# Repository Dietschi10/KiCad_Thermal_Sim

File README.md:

# KiCad Thermal Sim - Fast Multi-Layer Copper Thermal Simulation for KiCad

**KiCad Thermal Sim** is a lightweight KiCad PCB Editor plugin for fast, layout-oriented **heat spreading simulation across all copper layers** (`F.Cu` to `B.Cu`, including inner layers).

This is **not** a full 3D CFD/FEA solver. It is intended as a practical engineering tool to quickly answer:

- Where are the **hotspots** on each copper layer?
- How much do **copper pours/planes** and **via stitching** help?
- Which layout variant is **better** in an A/B comparison?
- How does heat distribute through the **stackup**?
- How much extra heat is created by **DC current flow** in copper?
- Which grid settings were actually used when automatic coarsening protects runtime?

---

## What It Simulates

- **2D in-plane conduction** on each copper layer.
- **Vertical coupling** between adjacent copper layers through FR4 and via enhancement.
- **Manual power injection** from explicitly configured **Heat Sources**.
- Constant pad power and time-varying **PWL power profiles**.
- Optional **DC current-flow heating** from source/sink pads on KiCad nets.
- **Convection** to ambient on top and bottom outer surfaces.
- Optional **Thermal Pad** geometry on `User.Eco1` for stronger bottom-side heat removal.
- Current-path diagnostics: copper loss, effective resistance, equivalent voltage drop, grid quality, and a Joule loss map.

---

## Installation

### Option A: KiCad Plugin Manager

1. Download the latest `ThermalSim-vX.Y.Z.zip` from the [Releases](https://github.com/PoeAlex/KiCad_Thermal_Sim/releases) page.
2. In KiCad, open **Plugin and Content Manager**.
3. Click **Install from File...** and select the downloaded ZIP.
4. Restart KiCad.
5. On first run, the plugin detects missing dependencies and offers to install them automatically.

### Option B: Manual Copy

1. Download or clone this repository.
2. Copy the plugin folder, meaning the folder that contains `__init__.py`, `thermal_plugin.py`, and the other `.py` modules, into KiCad's plugin directory:

   - **Windows**: `%APPDATA%\kicad\9.0\scripting\plugins\`
   - **Linux**: `~/.local/share/kicad/9.0/scripting/plugins/`
   - **macOS**: `~/Library/Application Support/kicad/9.0/scripting/plugins/`

3. Restart KiCad.
4. On first run, the plugin offers to install missing packages (`numpy`, `scipy`, `matplotlib`) automatically.

Alternatively, install packages manually in the **KiCad 9.0 Command Prompt**:

```bash
pip install numpy scipy matplotlib
```

Optional for faster large solves on supported Windows/Linux x86_64 systems:

```bash
pip install pypardiso
```

Run the plugin in PCB Editor via **Tools -> External Plugins -> 2.5D Thermal Sim**.

---

## Quick Start

1. Open your PCB in **KiCad PCB Editor**.
2. Select one or more pads if you want to pre-fill manual heat sources.
3. Run **Tools -> External Plugins -> 2.5D Thermal Sim**.
4. Use **Heat Sources** to add pads that dissipate manual power, then enter constant W values or PWL file paths.
5. Set **Duration**, **Ambient**, and **Resolution** on the **Overview** tab.
6. Optionally use **Current Heating** to add source/sink pads and per-pad currents for copper `I^2R` heating.
7. Optionally use **Advanced** for the simulation area, thermal pad, convection, and solver settings.
8. If current heating is enabled, click **Electrical Preview** to check current-net connectivity.
9. Click **Thermal Geometry Preview** to check the mapped board area, then **Run Simulation**.

---

## GUI Settings

The resizable dialog keeps board context and live preflight status visible above and below four compact tabs:

- **Overview** - duration, ambient temperature, target cell size, compute budget, live cost estimate, output, and collapsible board details.
- **Heat Sources** - manual heat sources selected independently from current terminals.
- **Current Heating** - DC current source/sink terminals for Joule heating.
- **Advanced** - collapsible simulation-area, thermal-pad, and solver settings.

The header summarizes the board, copper-layer count, heat sources, and current-balance state. The fixed footer shows the requested versus actual grid, readiness warnings, and the **Electrical Preview**, **Thermal Geometry Preview**, and **Run Simulation** actions. Electrical Preview is enabled when current heating has active terminals. Help and settings import/export are available from **More**. After a successful run, the dialog retains maximum temperature, elapsed time, and shortcuts to the report and output folder.

### Overview Tab

#### Board Info

Shows detected copper layers with thicknesses and dielectric gaps parsed from the board stackup. Pads selected when the dialog opened are shown only as a convenience; simulation roles are configured in **Heat Sources** and **Current Heating**.

#### Main Settings

- **Duration (sec)** - total simulated time. Shorter durations emphasize transient peaks; longer durations approach quasi steady-state.
- **Ambient Temp (C)** - reference temperature. Results are relative to ambient.
- **Target Cell Size (mm)** - desired spatial grid size. Smaller values improve hotspot and trace localization but increase runtime.
- **Compute Budget** - choose **Fast**, **Balanced**, **Detailed**, **Very detailed**, or **Custom**. The budget is based on total solver nodes across all copper layers.
- **Maximum Solver Nodes** - available in Custom mode for an explicit upper
  limit of up to 100 million equivalent uniform nodes. Values above 10 million
  are expert settings and may require tens of GB of RAM before adaptive
  reduction.

The live estimate shows requested versus actual cell size, grid dimensions, total nodes, approximate resolvable feature size, memory range, and a relative runtime class. For large boards, ThermalSim may automatically coarsen the requested cell size to remain within the selected budget. The report records the requested and actual resolution, compute budget, and simulated board fraction.

#### Output

- **Show All Layers** - display results for all copper layers.
- **Save Snapshots** - store intermediate temperature images.
- **Snapshot Count** - number of intermediate snapshots.
- **Output Folder** - where the timestamped result folder is created.

#### Settings Files

- **Load Settings...** - load a JSON settings file from any folder and apply it to the open dialog.
- **Save Settings...** - save the current dialog values as a JSON settings file.

ThermalSim also keeps using `thermal_sim_last_settings.json` in the plugin folder for automatic last-used settings. Manual load/save files use the same JSON structure and can be stored per project or per experiment.

### Heat Sources Tab

Manual pad power is configured separately from current-flow terminals.

1. Select pads in KiCad.
2. Click **Add Selected**.
3. Enter a power value or PWL file path in **Power / PWL**.
4. Use **Apply** to write the value to selected table rows. If no row is selected, a comma-separated list is applied in table order.

The Heat Sources table is:

| Column | Meaning |
|--------|---------|
| Pad | Footprint/pad name |
| Net | KiCad net name |
| Layer | Pad layer |
| Power W/PWL | Constant W value or PWL file path |

Accepted power entries:

| Entry | Meaning |
|-------|---------|
| `1.0` | 1 W constant on selected/listed power pads |
| `1.0, 0.5, 2.0` | Per-pad constant power in table order |
| `C:\sim\ramp.pwl` | Same PWL profile for selected/listed pads |
| `1.0, C:\sim\ramp.pwl` | Pad 1 = 1 W constant, Pad 2 = PWL file |

For backward compatibility, pads selected before opening the dialog pre-fill the Heat Sources table when no saved `power_pads` setting exists.

#### PWL File Format

PWL files are LTspice-style text files with two columns:

```text
; Comment lines start with ; or *
; Time(s)  Power(W)
0.0        0.0
0.001      1.0
0.005      2.5
0.010      2.5
0.020      0.0
```

- Time is in seconds.
- Power is in watts.
- Time values must be monotonically increasing.
- Power is linearly interpolated between points and held at the first/last value outside the defined range.

### Current Heating Tab

Enable current heating to calculate copper losses from DC current flow.

1. Select source/sink pads in KiCad.
2. Add them to a current group.
3. Enter positive current for source pads and negative current for sink pads.
4. Make sure every active KiCad net balances to `0 A`.

Current heating is additive with **Heat Sources**:

```text
total heat = manual pad power + calculated Joule copper loss
```

Power pads and current terminals may be different pads. Area limiting remains available with current heating: ThermalSim includes every pad, track, via/PTH, and filled zone belonging to the active current nets, then expands that geometry by the configured thermal margin. A large active plane may therefore require almost the full board.

The report shows **Path Current** as the useful current value. For a `+5 A` source and a `-5 A` sink, the path current is `5 A`. The internal sum of absolute terminal currents (`10 A` in that example) is kept only in raw diagnostics.

### Advanced Tab

#### Geometry Filters

- **Ignore Traces** - exclude copper traces from the conductivity map; zones, pours, and pads still contribute.
- **Limit to Active Sources and Current Paths** - crop the rectangular solver domain around heat sources and complete active current-net geometry.
- **Thermal Margin (mm)** - additional board area around sources and current paths. A practical starting point is 10-30 mm.

The preflight status shows the effective dimensions and percentage of the board. All copper inside the rectangular domain remains part of the thermal model. If active-net geometry cannot be inspected safely, ThermalSim falls back to the full board and reports a warning.

#### Thermal Pad (`User.Eco1`)

- **Enable Pad Simulation** - treat `User.Eco1` geometry as a thermal interface zone with enhanced bottom-side heat removal.
- **Pad Thickness (mm)** - thermal interface thickness.
- **Pad Cond. (W/mK)** - thermal interface conductivity.
- **Pad Heat Cap. (J/m2K)** - additional areal heat capacity.

#### Solver

- **Convection h (W/m2K)** - convection coefficient for top/bottom surfaces. Default is 10.
- **PCB Thickness (mm)** - overall board thickness. Stackup thickness is used when available.
- **Compute Engine** - `Auto` selects the matrix-free CPU engine for large jobs and keeps the legacy sparse solver for small jobs. Both engines remain manually selectable.
- **Spatial Mesh** - `Adaptive` keeps the requested cell size at copper edges, pads, vias, sources, and thermal-pad boundaries while merging homogeneous interiors. `Uniform` keeps the full regular grid.
- **Adaptive Max Cell Ratio** - largest adaptive cell relative to the requested cell size. The default is 8.
- **Capabilities** - detected solver backend, including the optional `thermalsim_core.dll`.

The **Balanced** compute budget is the default. Presets use total solver nodes, so a four-layer board automatically receives fewer 2D cells than a two-layer board at the same budget. **Custom** exposes one explicit maximum-node value; ThermalSim retains headroom when it must auto-coarsen.

The fast engine applies the finite-volume operator without constructing the
large global COO/CSR matrix used by the legacy direct solver. Adaptive runs use
a conservative reduced graph and geometrically coarsened multigrid
preconditioning. Reports show the equivalent uniform nodes, actual adaptive
nodes, reduction factor, PCG iterations, and residual.

---

## Previews

**Electrical Preview** checks active current-net connectivity and shows the solver's topology, graph raster, and copper occupancy. Use it before running current heating; it is enabled only when current heating has active terminals. It produces `electrical_connectivity_preview.png`, `electrical_graph_raster_preview.png`, and `electrical_copper_occupancy_preview.png`.

The synthetic regression board is available at `tests/demo/synthetic_electrical_connectivity_demo.kicad_pcb`.

**Thermal Geometry Preview** maps copper, power/current pads, vias, and the effective thermal simulation area. It does not run the thermal solver or show temperatures. Its header reports the cropped dimensions and percentage of the board.

Both previews use the copper-zone fills already stored by KiCad. If zones are stale or unfilled, press **B** in PCB Editor before previewing or running. The plugin does not refill zones automatically because this can block the interface for minutes on large boards and is unstable in some KiCad builds.

---

## Report Output

Each run creates a timestamped result folder, for example `Thermalsim_20260426_111121/`.

Typical files:

- `thermal_report.html` - main report with settings, stackup, diagnostics, images, and interactive heatmap.
- `thermal_preview.png` - mapped geometry preview.
- `thermal_stackup.png` or `thermal_final.png` - final temperature heatmap.
- `joule_loss_map.png` - current-induced copper loss map when current heating is active.
- `snap_*.png` - optional time-series snapshots.

### Current Path Diagnostics

When current heating is enabled, the HTML report includes **Current Path Diagnostics**:

- **Copper Loss** - total calculated Joule heating for active nets.
- **R_eff** - effective resistance, computed from `P / I_source^2`.
- **V_eq** - equivalent voltage drop, computed from `P / I_source`.
- **Source/Sink Current** - source and sink totals per active net.
- **Path Current** - useful current value for the path, not the doubled absolute terminal sum.
- **Net Path Metrics** - terminals, balance, loss, resistance, voltage drop, cell count, edge count, via edges, and copper islands.
- **Current Terminals** - pad positions, matched grid cells, island IDs, and mean potentials.
- **Mapped KiCad Primitives** - pads, tracks, vias/PTHs, zones, track length, and width summary.
- **Joule Loss Map** - per-layer static image of current-induced copper loss.

The report records requested and actual grid resolution, grid size, compute-budget preset, node budget, and the simulated percentage of the board.

---

## How to Interpret Results

This tool is most reliable for:

- **Relative comparisons** between layout variants.
- **Hotspot locations**.
- Trends from more copper, more vias, wider traces, or better spreading.
- Order-of-magnitude current-path loss and resistance diagnostics.

Absolute temperatures are **estimates** and depend strongly on modeling assumptions, grid resolution, board environment, airflow, and component/package thermal paths.

---

## Architecture

The plugin is split into focused modules:

| Module | Purpose |
|--------|---------|
| `capabilities.py` | Runtime detection of numpy, scipy, matplotlib, pypardiso, numba |
| `dependency_installer.py` | Auto-install dialog for missing packages via pip |
| `stackup_parser.py` | Parse copper/dielectric layers from `.kicad_pcb` S-expressions |
| `gui_dialogs.py` | wxPython dialog for simulation parameters |
| `geometry_mapper.py` | Accurately rasterize tracks, arcs, pads, vias, and filled zones |
| `adaptive_mesh.py` | Build conservative adaptive meshes and multigrid operators |
| `electrical_solver.py` | Solve DC current flow and convert copper losses to heat sources |
| `thermal_solver.py` | Legacy sparse and matrix-free PCG/BDF2 thermal solvers |
| `native_core.py` | Load the optional Windows x64 C++/OpenMP CPU core |
| `pwl_parser.py` | Parse LTspice-style PWL power profiles |
| `visualization.py` | Generate thermal plots, previews, heatmap payloads, and Joule loss maps |
| `thermal_report.py` | Generate the HTML report |
| `thermal_plugin.py` | Orchestrate workflow and KiCad ActionPlugin integration |

---

## Limitations

- No explicit component/package thermal model; junction-to-case-to-pad behavior is not modeled.
- Convection is simplified as uniform top/bottom ambient coupling.
- Radiation is not modeled.
- Current-flow heating is static DC only; AC effects, skin effect, and temperature-dependent copper resistance are not modeled.
- Current-path accuracy depends on grid resolution; narrow traces and small pads may need a finer grid to match hand calculations closely.
- Very fine requested resolutions may be auto-coarsened when the selected compute budget is exceeded.
- Via coupling is an approximation.
- Results depend strongly on **Target Cell Size**, **Compute Budget**, and the selected simulation area and thermal margin.
- Thermal Pad (`User.Eco1`) is a simplification of real contact pressure, interface quality, and sink temperature.

---

## Suggested Workflow

1. Add manual dissipating components in **Heat Sources**.
2. Add source/sink terminals in **Current Heating** only when copper `I^2R` heating matters.
3. Press **B** in PCB Editor so every copper zone has a current fill.
4. Enable **Limit to Active Sources and Current Paths** and start with a moderate thermal margin, for example 20 mm.
5. Check the effective board percentage; active current nets are always included completely.
6. Tune **Target Cell Size** until hotspots and current-path metrics are stable. Try 0.5 mm, then 0.3 mm.
7. Increase the **Compute Budget** only after checking the live node, memory, and runtime estimate.
8. Save JSON settings for repeatable project comparisons.
9. Compare layout variants using the same settings.
10. Validate important designs with measurement or a full 3D thermal workflow.

---

## Testing

Run the test suite from the repository root:

```bat
run_tests.bat
```

Run the synthetic large-grid benchmark without a proprietary board file:

```bash
python benchmark_fast_engine.py --nodes 10000000 --layers 4 --solve-steps 3
```

Legacy matrix construction is automatically skipped above the configured
safety limit. The benchmark reports equivalent/adaptive node counts, operator
build times, solve time, iteration counts, and process memory.

To build the optional native Windows CPU core, install Visual Studio Build
Tools with the C++ workload, then run:

```bash
cmake -S native -B native/build
cmake --build native/build --config Release
```

The generated `native/bin/thermalsim_core.dll` is included automatically by
`build_pcm_package.py`. Without the DLL, the same fast-engine interface uses
the NumPy/SciPy CPU implementation.

Useful variants:

```bat
run_tests.bat -k "test_thermal_solver"
run_tests.bat -m physics
run_tests.bat --cov=ThermalSim
```

### Real KiCad Benchmark

Use KiCad's bundled Python to benchmark a real board without saving or modifying it:

```powershell
& "C:\Program Files\KiCad\9.0\bin\python.exe" benchmark_real_board.py `
  "C:\path\to\board.kicad_pcb" --scenario thermal --time-stepping auto
```

Set `THERMALSIM_HEADLESS=1` when importing ThermalSim as a library outside PCB Editor. This prevents ActionPlugin registration while keeping the solver and board readers available.

---

## License / Disclaimer

MIT License

This plugin provides engineering estimates intended for fast iteration and comparative analysis. For safety-critical or thermally constrained designs, validate with measurement and/or a full 3D thermal tool.

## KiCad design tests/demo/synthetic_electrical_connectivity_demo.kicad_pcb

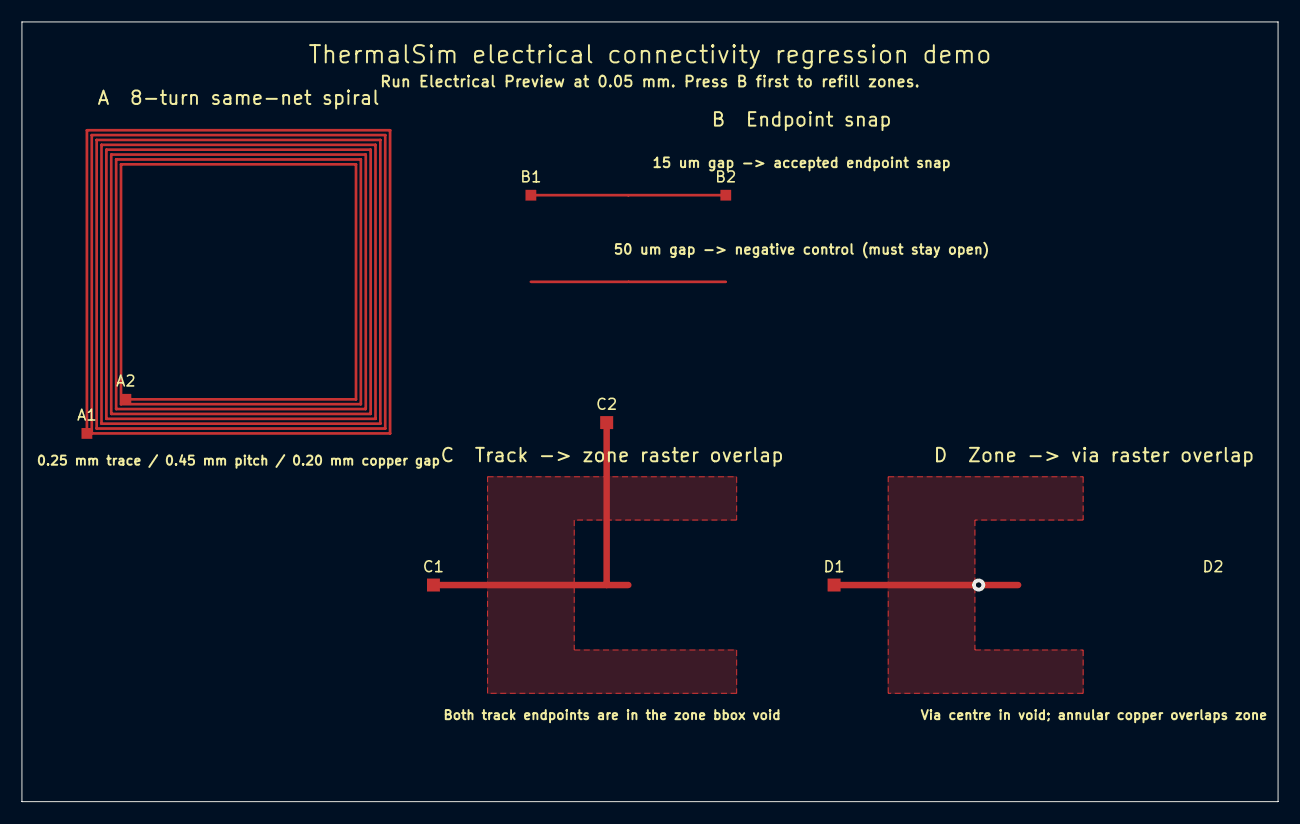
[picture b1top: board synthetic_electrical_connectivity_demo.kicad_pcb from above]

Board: 4 copper layers, 116.0 x 72.0 mm, 8 parts (0 on the bottom side), 4 nets.

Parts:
A1, A2: DEMO_A_8TURN_SPIRAL; Terminal
B1, B2: DEMO_B_15UM_SNAP; Terminal
C1, C2: DEMO_C_TRACK_ZONE; Terminal
D1, D2: DEMO_D_ZONE_VIA; Terminal

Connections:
DEMO_A_8TURN_SPIRAL: A1.1, A2.1
DEMO_B_15UM_SNAP: B1.1, B2.1
DEMO_C_TRACK_ZONE: C1.1, C2.1
DEMO_D_ZONE_VIA: D1.1, D2.1
